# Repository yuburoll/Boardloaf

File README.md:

# Boardloaf

36 key hotswappable split keyboard in 100x100 pcb

## Preparation

- 2x rp2040 zero (boards formly created by waveshare) (Approx. 4-8$)

- 2x Boardloaf PCB Boards (5 boards are 2$ on JLC w/o shipping cost)

- 1x printed case sets, which you want to make it (4$ for sandwitch, Approx. 12$ if you buy printed one)

- 36x diodes (Approx. 1$)

- (for V1) 32x M2x4 bolts, 16x M2x7 spacers (under 4mm radius) (Approx. 2$)

- (for V2) 16x M2x7 screws, flathead (can use M2x6 or M2x8) (Approx. 1$)

- 2x PJ320A 1/8(3.5mm) TRRS connector (Approx. 1$)

- 1x 1/8(3.5mm) TRRS cable (Approx. 2$, may TRS cable can take the place.)

- 36x MX Keyswitches & Keycaps & MX Hotswap Sockets (Maybe this cost varies too much. 10$ on average)

Approx. 26$-37$(w/o shipping cost) needed to build one.

## Build Guides

work in progress. sorry!

You can see the images in the folder, which uploaded for build guides. Especially you may see how to solder the controller board, because this uses surface mounting by castelated pins.

Images are captured with prototype version PCB, which is different from the current gerber. Current gerber has two "Jump when back side" jumper point on each side, to check which hand is on the position. You may see diode jumper on assembly image for the same role, and you don't need to jump via diodes if you jump jumpers correctly.

This uses [qmk](https://qmk.fm/) to build the firmware. Copy "boardloaf" folder which is in "firmware/qmk" directory to "qmk_firmware\keyboards" folder, and build it via qmk msys.

Or, simply flash uf2 in "uf2Examples" folder by changing rp2040 zero in dfu mode, which can be executed by holding boot button while plugging in usb c. Vial versions are also prepared.

## Licenses

miryoku keymap follows GNU GPL 2.0 license.

all other codes follow MIT license.

all designs and the hardware board follow CC BY-SA 4.0 license.

If you want to make a commercial product, it would be appreciated if you sponsor some bucks for me.

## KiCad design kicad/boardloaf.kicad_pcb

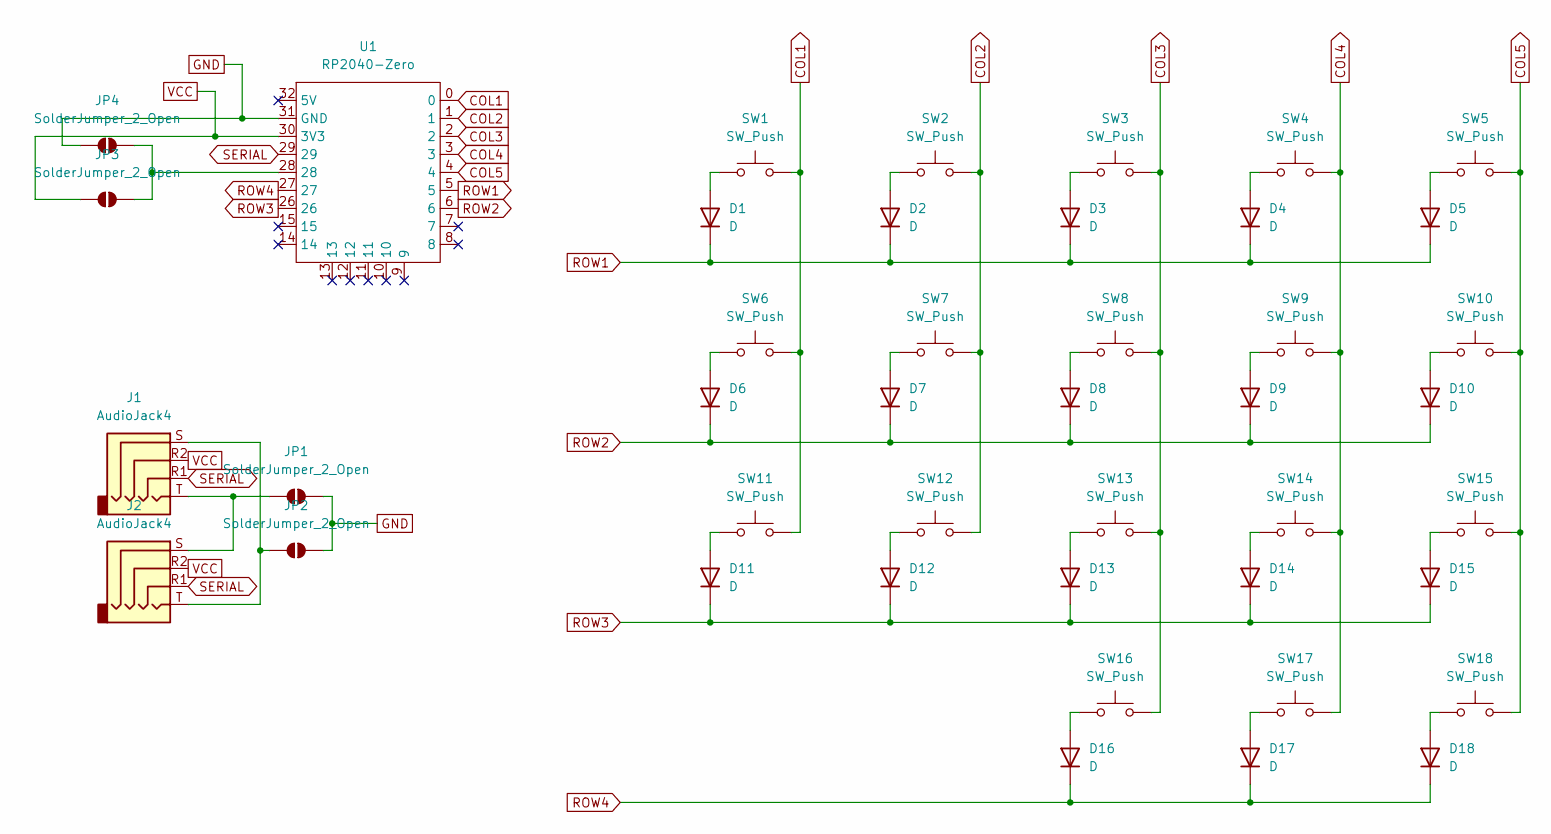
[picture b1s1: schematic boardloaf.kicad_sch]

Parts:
D1, D2, D3, D4, D5, D6, D7, D8, D9, D10, D11, D12, D13, D14, D15, D16, D17, D18: D
J1, J2: AudioJack4
JP1, JP2, JP3, JP4: SolderJumper_2_Open
SW1, SW2, SW3, SW4, SW5, SW6, SW7, SW8, SW9, SW10, SW11, SW12, SW13, SW14, SW15, SW16, SW17, SW18: SW_Push
U1: RP2040-Zero

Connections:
COL1: SW1.2, SW6.2, SW11.2, U1.0
COL2: SW2.2, SW7.2, SW12.2, U1.1
COL3: SW3.2, SW8.2, SW13.2, SW16.2, U1.2
COL4: SW4.2, SW9.2, SW14.2, SW17.2, U1.3
COL5: SW5.2, SW10.2, SW15.2, SW18.2, U1.4
GND: JP1.2 (B), JP2.2 (B), JP4.1 (A), U1.31 (GND)
unnamed: D1.2 (A), SW1.1
unnamed: D2.2 (A), SW2.1
unnamed: D3.2 (A), SW3.1
unnamed: D4.2 (A), SW4.1
unnamed: D5.2 (A), SW5.1
unnamed: D6.2 (A), SW6.1
unnamed: D7.2 (A), SW7.1
unnamed: D8.2 (A), SW8.1
unnamed: D9.2 (A), SW9.1
unnamed: D10.2 (A), SW10.1
unnamed: D11.2 (A), SW11.1
unnamed: D12.2 (A), SW12.1
unnamed: D13.2 (A), SW13.1
unnamed: D14.2 (A), SW14.1
unnamed: D15.2 (A), SW15.1
unnamed: D16.2 (A), SW16.1
unnamed: D17.2 (A), SW17.1
unnamed: D18.2 (A), SW18.1
unnamed: J1.T, J2.S, JP1.1 (A)
unnamed: J1.S, J2.T, JP2.1 (A)
unnamed: JP3.2 (B), JP4.2 (B), U1.28
ROW1: D1.1 (K), D2.1 (K), D3.1 (K), D4.1 (K), D5.1 (K), U1.5
ROW2: D6.1 (K), D7.1 (K), D8.1 (K), D9.1 (K), D10.1 (K), U1.6
ROW3: D11.1 (K), D12.1 (K), D13.1 (K), D14.1 (K), D15.1 (K), U1.26
ROW4: D16.1 (K), D17.1 (K), D18.1 (K), U1.27
SERIAL: J1.R1, J2.R1, U1.29
VCC: J1.R2, J2.R2, JP3.1 (A), U1.30 (3V3)

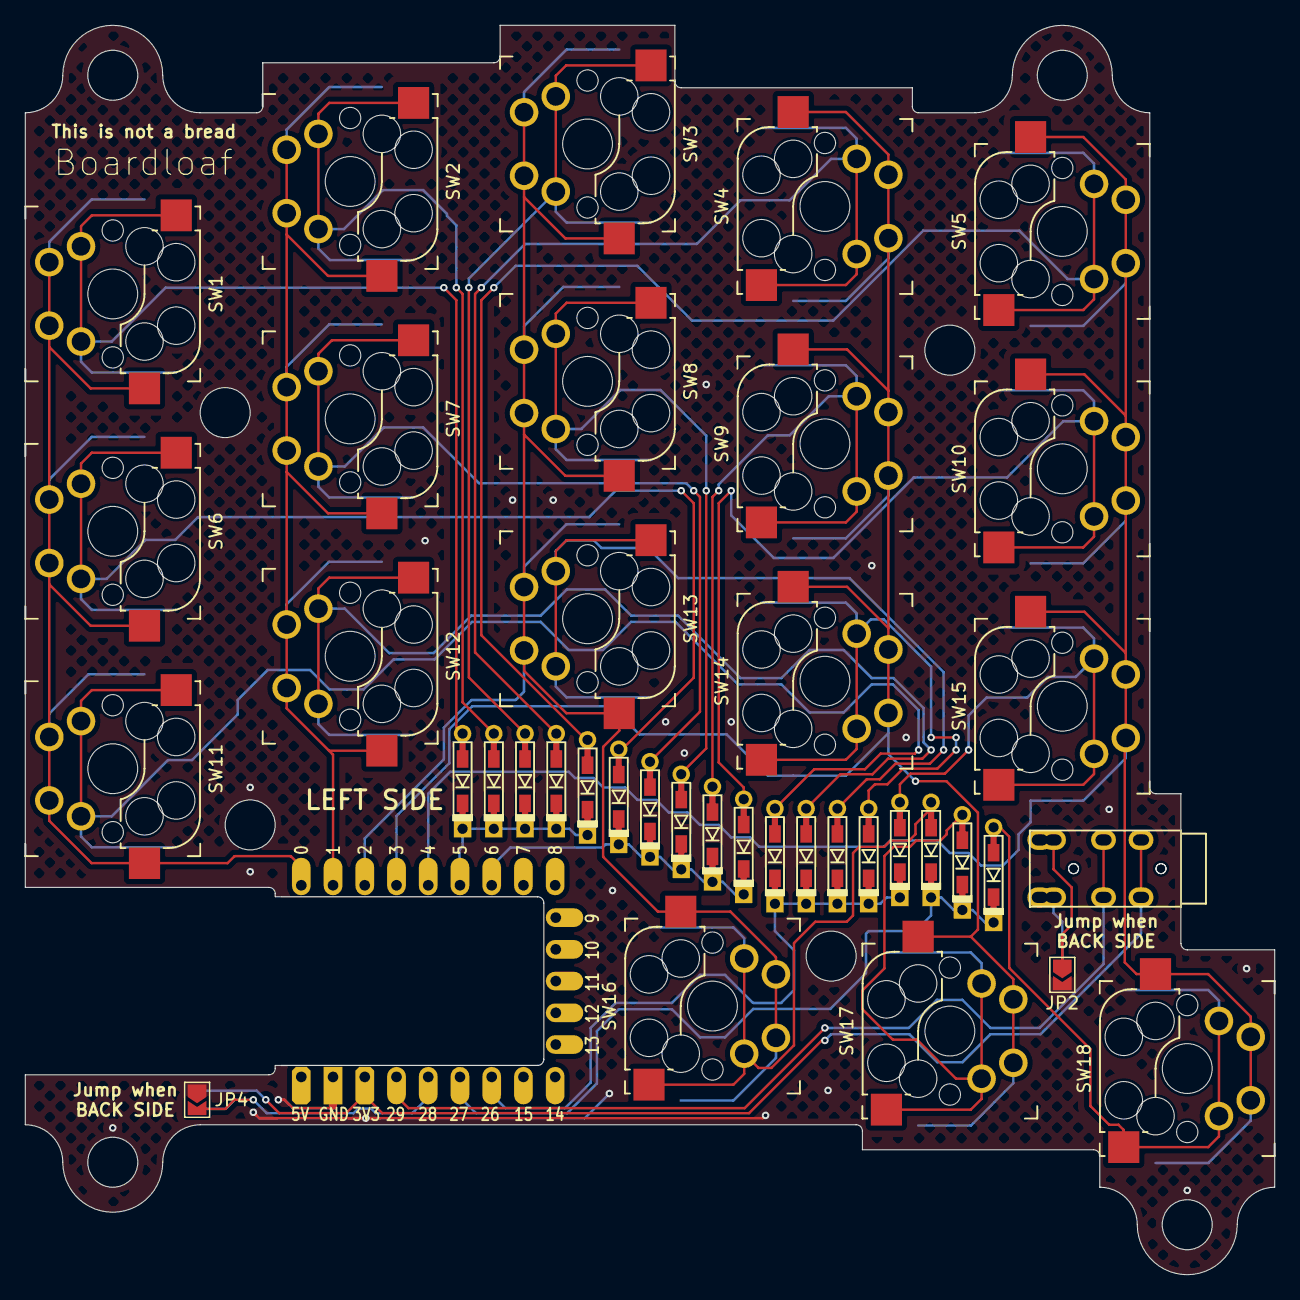
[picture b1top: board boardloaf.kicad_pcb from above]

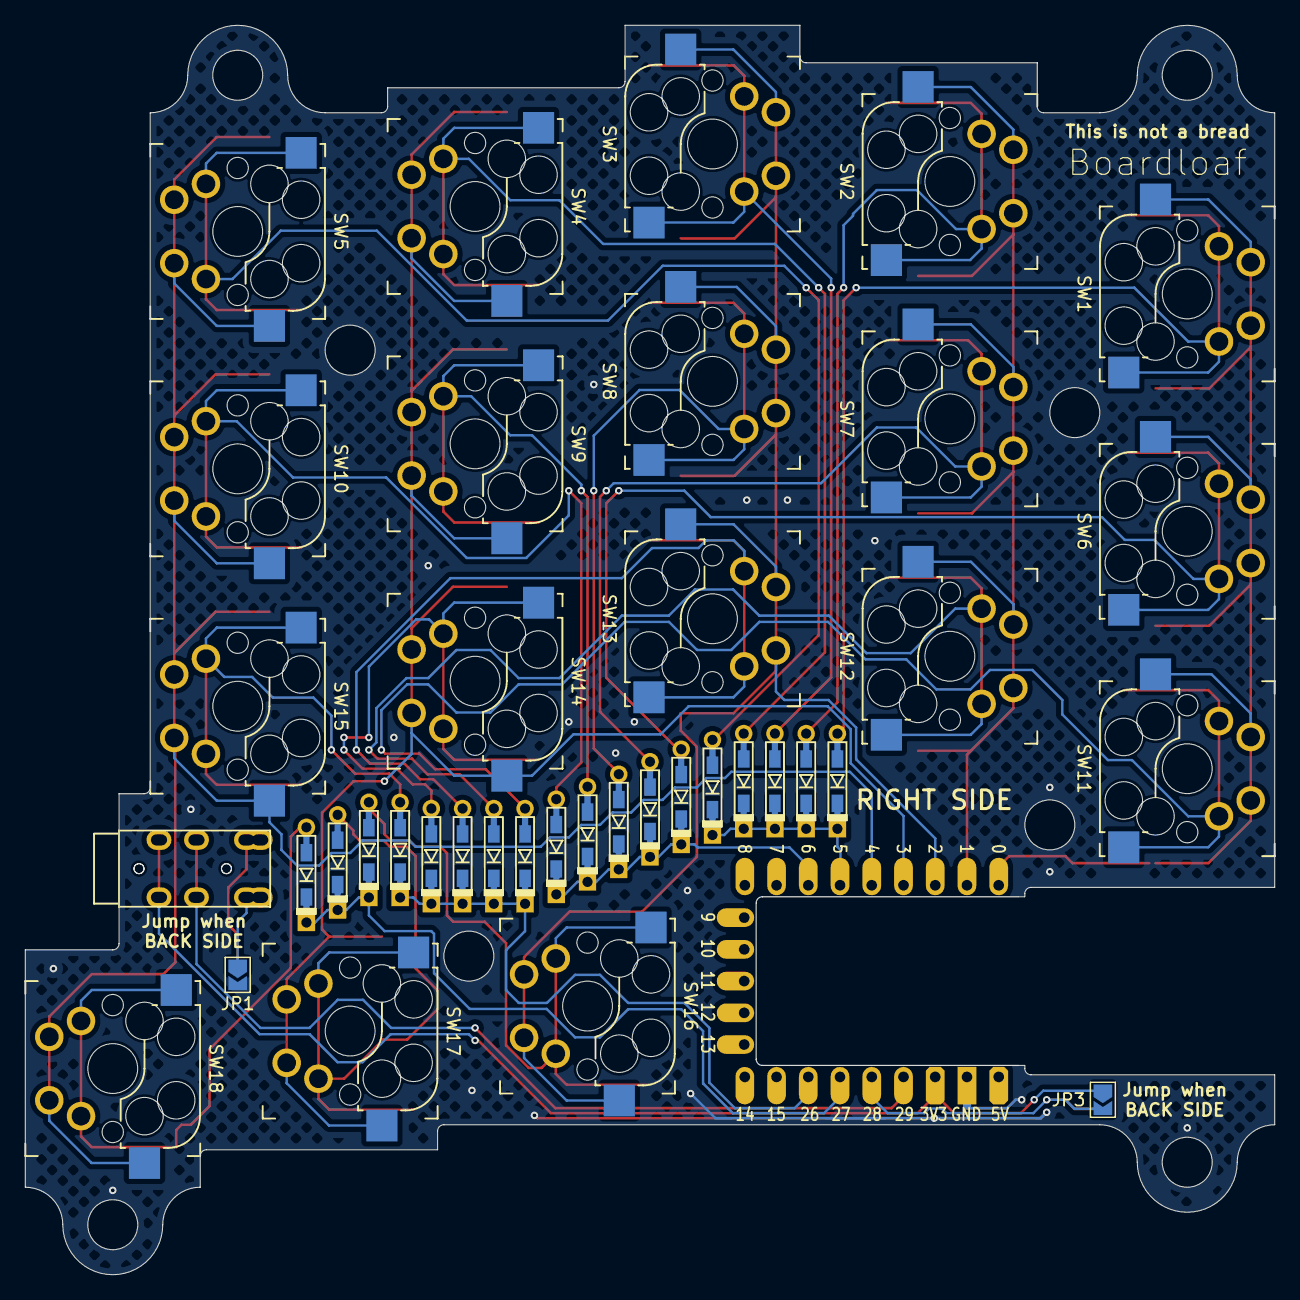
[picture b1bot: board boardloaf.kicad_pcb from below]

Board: 2 copper layers, 100.0 x 100.0 mm, 43 parts (3 on the bottom side), 33 nets.

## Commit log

2025-11-04 upload gubberjob and kicad
2025-11-04 upload backplate
2025-11-04 align hole
2025-11-08 add gitignore
2025-11-09 upload printable case
2025-11-09 upload plate case
2025-11-09 change position of case file
2025-11-09 update firmware
2025-11-09 made jumper for reverse
2025-11-09 update firmware for jumper
2025-11-09 update gubber files
2025-11-09 get back to once you belong
2025-11-10 fix schema and add jumper
2025-11-10 update gubber
2025-11-10 update ground route and gubber
2025-11-20 update case
2025-11-22 add vial and miryoku
2025-11-22 upload images
2025-11-22 fix keymap name
2025-11-22 change main image
